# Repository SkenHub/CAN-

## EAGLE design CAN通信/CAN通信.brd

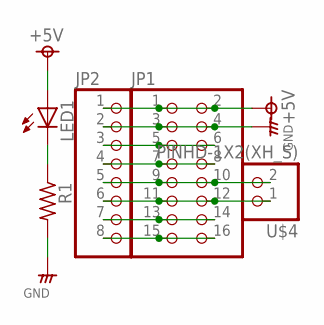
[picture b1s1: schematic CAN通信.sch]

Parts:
JP1: PINHD-2X8; 2X08
JP2: PINHD-1X8; 1X08
LED1: LED3MM
R1: RESISTORS-3; R_0.3
U$4: PINHD-1X2(XH_S); 1X2(XH-S)

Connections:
+5V: JP1.1, JP1.2, JP2.1, LED1.A
GND: JP1.3, JP1.4, JP2.2, R1.2
unnamed: LED1.K (C), R1.1
unnamed: JP1.5, JP1.6, JP2.3
unnamed: JP1.7, JP1.8, JP2.4
unnamed: JP1.9, JP1.10, JP2.5, U$4.2
unnamed: JP1.11, JP1.12, JP2.6, U$4.1
unnamed: JP1.13, JP1.14, JP2.7
unnamed: JP1.15, JP1.16, JP2.8

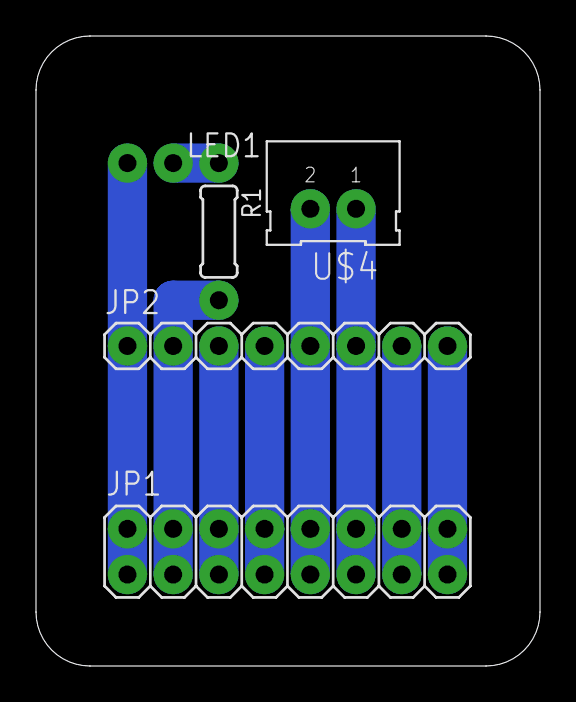
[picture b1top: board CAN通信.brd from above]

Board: 2 copper layers, 28.0 x 35.0 mm, 5 parts (0 on the bottom side), 9 nets.
